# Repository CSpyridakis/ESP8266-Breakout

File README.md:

# ESP8266-Breakout  

A breadboard-friendly ESP12E/F breakout with all I/O pins available, flash/reset buttons onboard, and place to directly use it with FTDI modules like [FT232RL FTDI Serial Adapter Module](https://www.banggood.com/FT232RL-FTDI-USB-To-TTL-Serial-Converter-Adapter-Module-p-917226.html?rmmds=buy&cur_warehouse=CN).

### Schematic

|Top View             |  Bottom View              |
|:-------------------:|:-------------------------:|
|  |  |

### Sample

## Assembly 
| No  |   Component   |    Quantity      |
|:---:|:-------------:|:----------------:|
| 1.  |      ESP8266 - 12e/f         | 1 | 
| 2.  |    10KΩ 0805 smd resistors   | 5 | 
| 3.  |      SMD-SWITCH-6.2MM        | 2 |
| 4.  | Pin Header 1x11 Male 2.54 mm | 2 |

### Notes
* If you want to power up ESP8266-Breakout directly from a FTDI board, you need to solder the jumper that exists on the bottom side of the ESP8266-Breakout. **IMPORTANT:** Do not forget to change the jumper to 3.3V instead of 5V, on the FTDI module.
* If you want to use ESP8266-Breakout with a breadboard.
  - Connect Vcc to 3.3V
  - Connect Gn to Ground
  - You do not need to connect EN pin (ESP8266-Breakout itself has the required connection)
  - You do not need to add any extra pull-up or pull-down resistors on GPIO15, GPIO2 or GPIO0 for Boot Mode Selection

## PCB CAD tool
This project was developed using free version of  [EAGLE 9.5.2](https://www.autodesk.com/products/eagle/overview)

Gerber files are available [here](pcb/gerber/)

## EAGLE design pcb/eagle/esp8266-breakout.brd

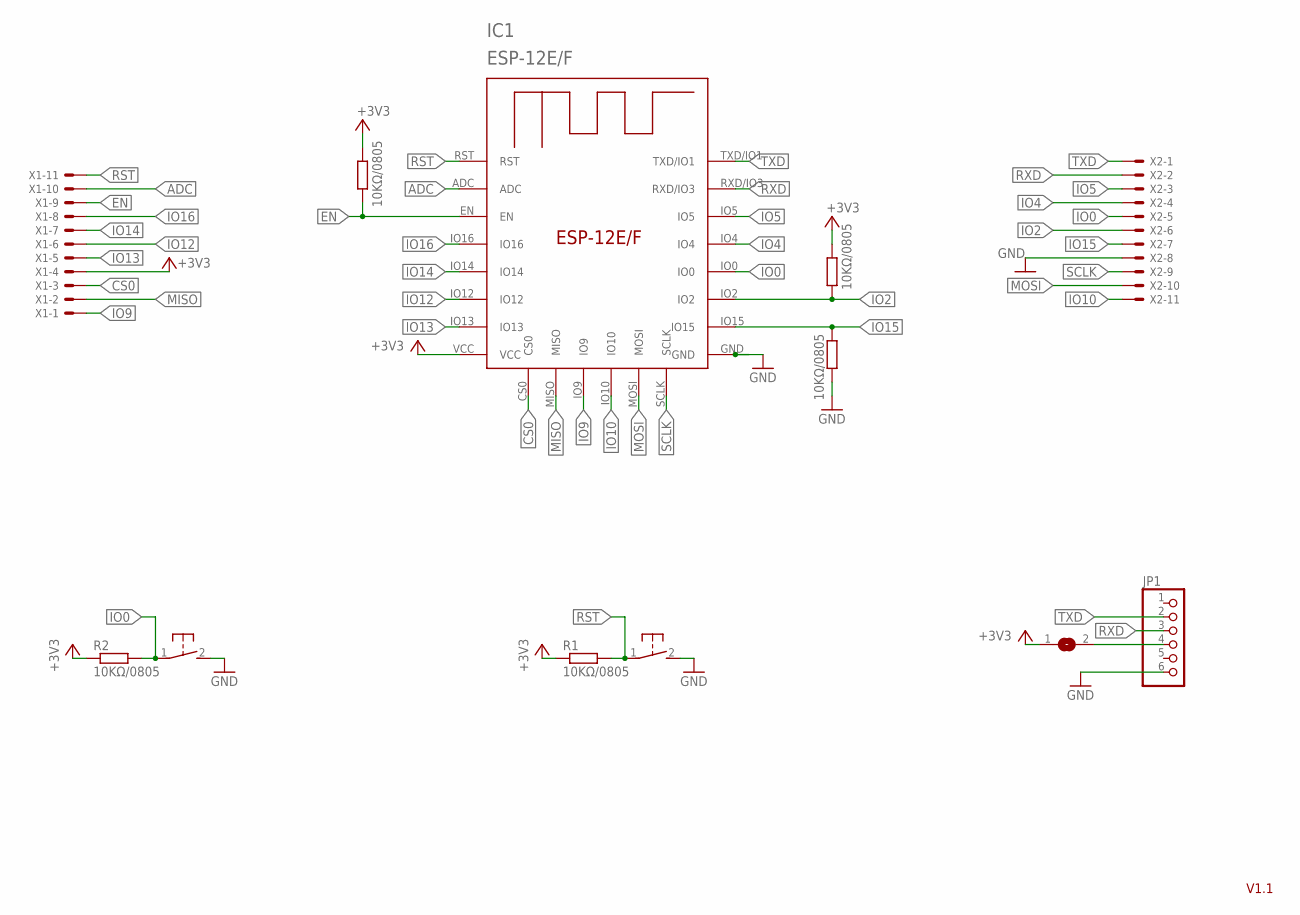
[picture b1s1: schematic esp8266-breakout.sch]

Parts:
IC1: ESP-12E/F; ESP-12E
JP1: PINHD-1X6B; 1X06-BIG
R1, R2, R3, R4, R5: 10KΩ/0805; R0805
S1, S2: DTSM-3
SJ1: SJ
X1, X2: JST-XH-11-PIN-ROUND-PAD; JST-XH-11-PACKAGE-ROUND-PAD

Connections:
+3V3: IC1.VCC, R1.1, R2.1, R4.1, R5.1, SJ1.1, X1.4
ADC: IC1.ADC, X1.10
CS0: IC1.CS0, X1.3
EN: IC1.EN, R5.2, X1.9
GND: IC1.GND, JP1.6, R3.2, S1.2, S2.2, X2.8
IO0: IC1.IO0, R2.2, S2.1, X2.5
IO2: IC1.IO2, R4.2, X2.6
IO4: IC1.IO4, X2.4
IO5: IC1.IO5, X2.3
IO9: IC1.IO9, X1.1
IO10: IC1.IO10, X2.11
IO12: IC1.IO12, X1.6
IO13: IC1.IO13, X1.5
IO14: IC1.IO14, X1.7
IO15: IC1.IO15, R3.1, X2.7
IO16: IC1.IO16, X1.8
MISO: IC1.MISO, X1.2
MOSI: IC1.MOSI, X2.10
unnamed: JP1.4, SJ1.2
RST: IC1.RST, R1.2, S1.1, X1.11
RXD: IC1.RXD/IO3, JP1.3, X2.2
SCLK: IC1.SCLK, X2.9
TXD: IC1.TXD/IO1, JP1.2, X2.1

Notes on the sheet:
V1.1

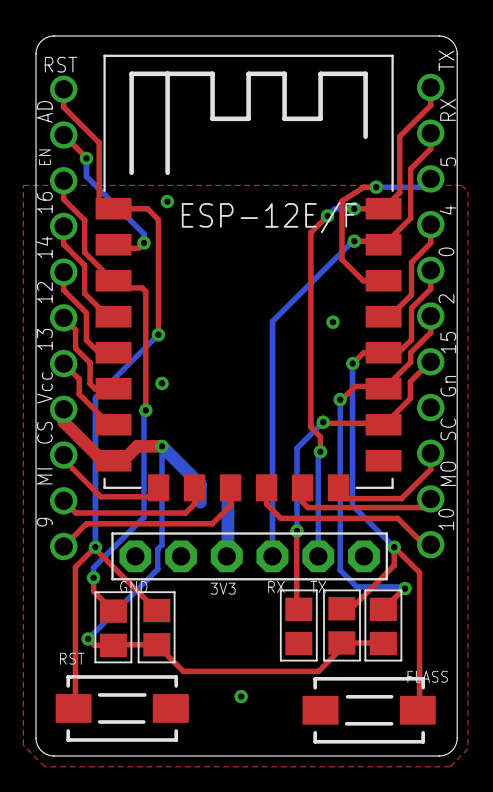
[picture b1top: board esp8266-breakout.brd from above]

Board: 2 copper layers, 23.4 x 40.0 mm, 12 parts (1 on the bottom side), 23 nets.

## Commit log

2020-03-15 Pcb v1
2020-03-17 Rev 1
2020-03-17 Minor changes
2020-03-17 Round corners added
2020-03-17 Version 1.1
2020-03-17 V1.1 Done
2020-03-17 Remove BUs, Rev 1.1 Completed (TODO recheck)
2020-03-17 Doc updated
2020-03-17 Added perimeter on resistors
2020-03-17 Fix license typo
2020-04-29 Readme updated, photos added
2020-05-03 Top/Bottom pcb photos updated

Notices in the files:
README.md:
MIT license
pcb/eagle/esp8266-breakout.brd:
Rev.1.1 (C) 2020
